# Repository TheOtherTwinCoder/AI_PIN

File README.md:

## Nudge, a better AI Pin
Hey everyone! For Outpost, I'm creating an AI Pin, but not like Humane's failed attempt...

AI's creating a revolution throughout the world, and in early 2025, I (along with many others) saw the Humane AI Pin for the first time! It was revolutionary, but four harsh parts of the device stood out:

- Cloud AI Processing
- Needed a SIM Card
- Forced users into a subscription
- WAS $699!!
  
For this reason, I'm setting out to create the better version that doesn't need any of those reqirements - and as I'm calling it, Nudge!

IDEAS for Nudge:

- "Hey Nudge" for wake up
- Ability to take pictures and process them with AI
- Ask questions to Nudge, with relatively quick responses
- On device processing (no WiFi!)

Let's get on with it, shall we? I do need Super Hardware Builder Status, but I'll do that when I get back from vacation (July 4th).

BOM:
| Designator | Footprint | Quantity | Value | LCSC Part # | Price | Total |
|---|---|---|---|---|---|---|
| SW1 | SW_Slide-03_Wuerth-WS-SLTV_10x2.5x6.4_P2.54mm | 1 | SW_Wuerth_450301014042 | C2985934 | $4.50 | |
| U1 | XIAO-ESP32-S3-SMD | 1 | XIAO-ESP32-S3-SMD | - | $27.98 | |
| U3 | adafruit-MAX98357 | 1 | adafruit-MAX98357 | - | $7.59 | |
| - | JLCPCB | 1 | JLCPCB | - | $44.96 | |
| - | Shipping + Tariffs | - | - | - | $8.49 | |
| - | - | - | - | - | - | **$98.86** |

Images:

The XIAO Sense:

Slide Switch:

Actual Adafruit MAX Amp:

Whole Schematic:

PCB Revision 3: (Routed + Silkscreen)

A few BOM screenshots:

JLCPCB:

AliExpress:

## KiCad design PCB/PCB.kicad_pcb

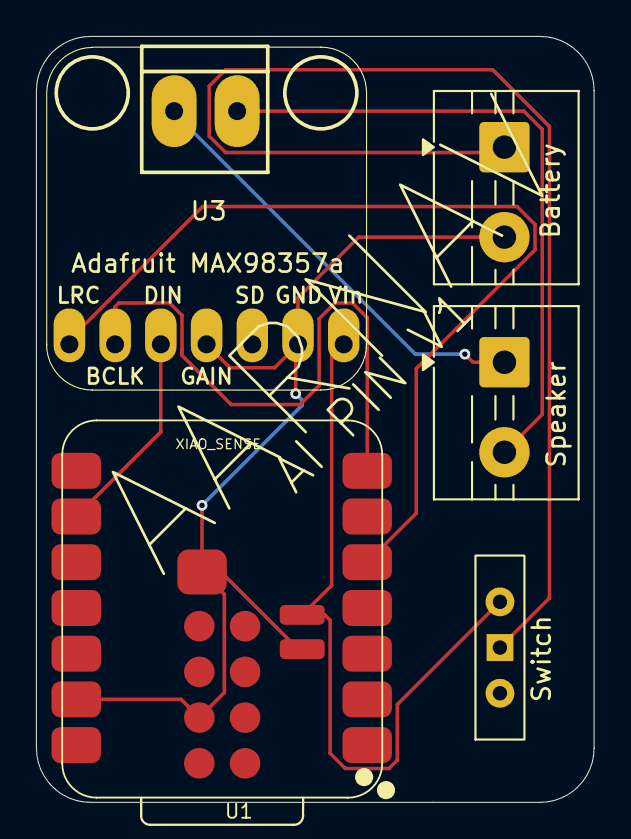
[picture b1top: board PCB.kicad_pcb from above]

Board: 2 copper layers, 31.0 x 42.5 mm, 5 parts (0 on the bottom side), 8 nets.

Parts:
BT1: Battery_Cell; TerminalBlock_MaiXu_MX126-5.0-02P_1x02_P5.00mm
LS2: Speaker; TerminalBlock_MaiXu_MX126-5.0-02P_1x02_P5.00mm
Switch: SW_Wuerth_450301014042; SW_Slide-03_Wuerth-WS-SLTV_10x2.5x6.4_P2.54mm
U1: XIAO-ESP32-S3-SMD
U3: adafruit-MAX98357

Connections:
D4: U1.5 (D4), U3.7 (LRC)
D6: U1.7 (D6), U3.6 (BCLK)
D8: U1.9 (D8), U3.5 (DIN)
GND: BT1.2 (-), U1.13 (GND), U1.18 (GND), U1.24 (GND), U1.25 (PAD), U3.2 (GND), U3.4 (GAIN)
unnamed: BT1.1 (+), Switch.1 (B)
unnamed: LS2.2, U3.9 (OUTN)
unnamed: LS2.1, U3.8 (OUTP)
VBAT: Switch.3 (A), U1.23 (VBAT), U3.1 (Vin)

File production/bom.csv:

Designator,Footprint,Quantity,Value,LCSC Part #
BT1,TerminalBlock_MaiXu_MX126-5.0-02P_1x02_P5.00mm,1,Battery_Cell,
LS2,TerminalBlock_MaiXu_MX126-5.0-02P_1x02_P5.00mm,1,Speaker,
SWITCH,SW_Slide-03_Wuerth-WS-SLTV_10x2.5x6.4_P2.54mm,1,SW_Wuerth_450301014042,
U1,XIAO-ESP32-S3-SMD,1,XIAO-ESP32-S3-SMD,
U3,adafruit-MAX98357,1,adafruit-MAX98357,
